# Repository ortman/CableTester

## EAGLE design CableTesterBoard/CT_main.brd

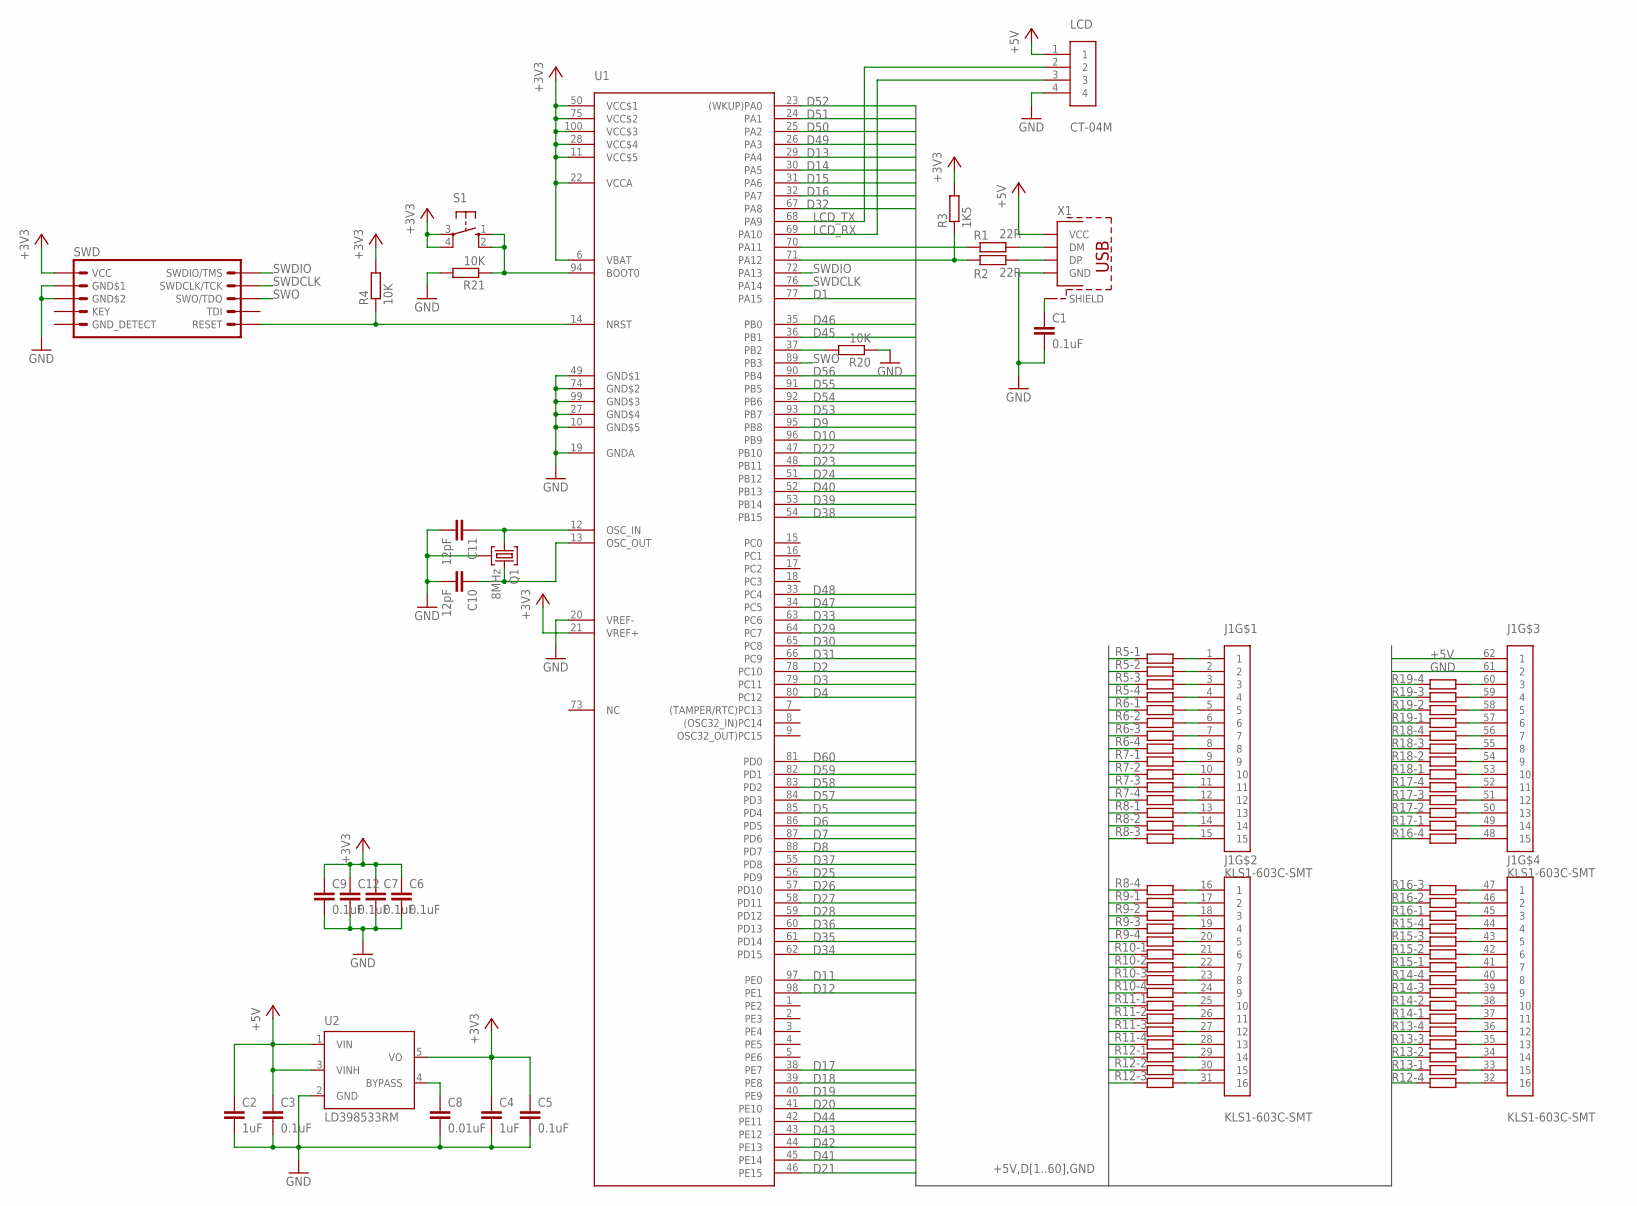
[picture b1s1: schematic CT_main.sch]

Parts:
C1, C3, C5, C6, C7, C9, C12: 0.1uF; C0603
C2, C4: 1uF; C0603
C8: 0.01uF; C0603
C10, C11: 12pF; C0603
J1: KLS1-603C-SMT
LCD: CT-04M
Q1: 8MHz; KX-7_12.XXXXX
R1, R2: 22R; R0603
R3: 1K5; R0603
R4, R20, R21: 10K; R0603
R5, R6, R7, R8, R9, R10, R11, R12, R13, R14, R15, R16, R17, R18, R19: R_EU_4_R1206; R1206_4
S1: 10-XXDTSM-20; DTSM20
SWD: JTAG/SWD_10PIN; ML10
U1: STM32F1xx; LQFP100
U2: LD398533RM; SOT23-5L
X1: USBMICRO-B; MOLEX-47364-0001

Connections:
+3V3: C4.1, C5.1, C6.1, C7.1, C9.1, C12.1, R3.2, R4.2, S1.3, S1.4 (P1), SWD.1 (VCC), U1.6 (VBAT), U1.11 (VCC$5), U1.21 (VREF+), U1.22 (VCCA), U1.28 (VCC$4), U1.50 (VCC$1), U1.75 (VCC$2), U1.100 (VCC$3), U2.5 (VO)
+5V: C2.1, C3.1, J1.62 (1), LCD.1, U2.1 (VIN), U2.3 (VINH), X1.1 (VCC)
D1: R5.8 (2), U1.77 (PA15)
D2: R5.7 (2), U1.78 (PC10)
D3: R5.6 (2), U1.79 (PC11)
D4: R5.5 (2), U1.80 (PC12)
D5: R6.8 (2), U1.85 (PD4)
D6: R6.7 (2), U1.86 (PD5)
D7: R6.6 (2), U1.87 (PD6)
D8: R6.5 (2), U1.88 (PD7)
D9: R7.8 (2), U1.95 (PB8)
D10: R7.7 (2), U1.96 (PB9)
D11: R7.6 (2), U1.97 (PE0)
D12: R7.5 (2), U1.98 (PE1)
D13: R8.8 (2), U1.29 (PA4)
D14: R8.7 (2), U1.30 (PA5)
D15: R8.6 (2), U1.31 (PA6)
D16: R8.5 (2), U1.32 (PA7)
D17: R9.8 (2), U1.38 (PE7)
D18: R9.7 (2), U1.39 (PE8)
D19: R9.6 (2), U1.40 (PE9)
D20: R9.5 (2), U1.41 (PE10)
D21: R10.8 (2), U1.46 (PE15)
D22: R10.7 (2), U1.47 (PB10)
D23: R10.6 (2), U1.48 (PB11)
D24: R10.5 (2), U1.51 (PB12)
D25: R11.8 (2), U1.56 (PD9)
D26: R11.7 (2), U1.57 (PD10)
D27: R11.6 (2), U1.58 (PD11)
D28: R11.5 (2), U1.59 (PD12)
D29: R12.8 (2), U1.64 (PC7)
D30: R12.7 (2), U1.65 (PC8)
D31: R12.6 (2), U1.66 (PC9)
D32: R12.5 (2), U1.67 (PA8)
D33: R13.1, U1.63 (PC6)
D34: R13.2 (1), U1.62 (PD15)
D35: R13.3 (1), U1.61 (PD14)
D36: R13.4 (1), U1.60 (PD13)
D37: R14.1, U1.55 (PD8)
D38: R14.2 (1), U1.54 (PB15)
D39: R14.3 (1), U1.53 (PB14)
D40: R14.4 (1), U1.52 (PB13)
D41: R15.1, U1.45 (PE14)
D42: R15.2 (1), U1.44 (PE13)
D43: R15.3 (1), U1.43 (PE12)
D44: R15.4 (1), U1.42 (PE11)
D45: R16.1, U1.36 (PB1)
D46: R16.2 (1), U1.35 (PB0)
D47: R16.3 (1), U1.34 (PC5)
D48: R16.4 (1), U1.33 (PC4)
D49: R17.1, U1.26 (PA3)
D50: R17.2 (1), U1.25 (PA2)
D51: R17.3 (1), U1.24 (PA1)
D52: R17.4 (1), U1.23 ((WKUP)PA0)
D53: R18.1, U1.93 (PB7)
D54: R18.2 (1), U1.92 (PB6)
D55: R18.3 (1), U1.91 (PB5)
D56: R18.4 (1), U1.90 (PB4)
D57: R19.1, U1.84 (PD3)
D58: R19.2 (1), U1.83 (PD2)
D59: R19.3 (1), U1.82 (PD1)
D60: R19.4 (1), U1.81 (PD0)
GND: C1.2, C2.2, C3.2, C4.2, C5.2, C6.2, C7.2, C8.2, C9.2, C10.2, C11.2, C12.2, J1.61 (2), LCD.4, Q1.2, Q1.4 (2), R20.1, R21.2, SWD.3 (GND$1), SWD.5 (GND$2), U1.10 (GND$5), U1.19 (GNDA), U1.20 (VREF-), U1.27 (GND$4), U1.49 (GND$1), U1.74 (GND$2), U1.99 (GND$3), U2.2 (GND), X1.5 (GND)
GND_DETECT: SWD.9 (GND_DETECT)
LCD_RX: LCD.3, U1.69 (PA10)
LCD_TX: LCD.2, U1.68 (PA9)
unnamed: R1.2, X1.2 (DM)
unnamed: R2.2, X1.3 (DP)
unnamed: C8.1, U2.4 (BYPASS)
unnamed: J1.1, R5.1
unnamed: R1.1, U1.70 (PA11)
unnamed: R2.1, R3.1, U1.71 (PA12)
unnamed: R4.1, SWD.10 (RESET), U1.14 (NRST)
unnamed: C10.1, Q1.3, U1.13 (OSC_OUT)
unnamed: C11.1, Q1.1, U1.12 (OSC_IN)
unnamed: J1.2, R5.2 (1)
unnamed: J1.3, R5.3 (1)
unnamed: J1.4, R5.4 (1)
unnamed: J1.8, R6.4 (1)
unnamed: J1.7, R6.3 (1)
unnamed: J1.6, R6.2 (1)
unnamed: J1.5, R6.1
unnamed: J1.9, R7.1
unnamed: J1.10, R7.2 (1)
unnamed: J1.11, R7.3 (1)
unnamed: J1.12, R7.4 (1)
unnamed: J1.13, R8.1
unnamed: J1.17 (2), R9.1
unnamed: J1.18 (3), R9.2 (1)
unnamed: J1.19 (4), R9.3 (1)
unnamed: J1.20 (5), R9.4 (1)
unnamed: J1.21 (6), R10.1
unnamed: J1.22 (7), R10.2 (1)
unnamed: J1.23 (8), R10.3 (1)
unnamed: J1.27 (12), R11.3 (1)
unnamed: J1.28 (13), R11.4 (1)
unnamed: J1.29 (14), R12.1
unnamed: J1.30 (15), R12.2 (1)
unnamed: J1.31 (16), R12.3 (1)
unnamed: J1.26 (11), R11.2 (1)
unnamed: J1.25 (10), R11.1
unnamed: J1.24 (9), R10.4 (1)
unnamed: J1.14, R8.2 (1)
unnamed: J1.15, R8.3 (1)
unnamed: J1.16 (1), R8.4 (1)
unnamed: J1.32 (16), R12.4 (1)
unnamed: J1.33 (15), R13.8 (2)
unnamed: J1.34 (14), R13.7 (2)
unnamed: J1.35 (13), R13.6 (2)
unnamed: J1.36 (12), R13.5 (2)
unnamed: J1.37 (11), R14.8 (2)
unnamed: J1.38 (10), R14.7 (2)
unnamed: J1.39 (9), R14.6 (2)
unnamed: J1.40 (8), R14.5 (2)
unnamed: J1.41 (7), R15.8 (2)
unnamed: J1.42 (6), R15.7 (2)
unnamed: J1.43 (5), R15.6 (2)
unnamed: J1.44 (4), R15.5 (2)
unnamed: J1.45 (3), R16.8 (2)
unnamed: J1.46 (2), R16.7 (2)
unnamed: J1.47 (1), R16.6 (2)
unnamed: J1.60 (3), R19.5 (2)
unnamed: J1.59 (4), R19.6 (2)
unnamed: J1.58 (5), R19.7 (2)
unnamed: J1.57 (6), R19.8 (2)
unnamed: J1.56 (7), R18.5 (2)
unnamed: J1.55 (8), R18.6 (2)
unnamed: J1.54 (9), R18.7 (2)
unnamed: J1.53 (10), R18.8 (2)
unnamed: J1.52 (11), R17.5 (2)
unnamed: J1.51 (12), R17.6 (2)
unnamed: J1.50 (13), R17.7 (2)
unnamed: J1.49 (14), R17.8 (2)
unnamed: J1.48 (15), R16.5 (2)
unnamed: R20.2, U1.37 (PB2)
unnamed: R21.1, S1.1 (S), S1.2 (S1), U1.94 (BOOT0)
SHIELD: C1.1, X1.GND1 (SHIELD), X1.GND2 (SHIELD), X1.GND3 (SHIELD), X1.GND4 (SHIELD)
SWDCLK: SWD.4 (SWDCLK/TCK), U1.76 (PA14)
SWDIO: SWD.2 (SWDIO/TMS), U1.72 (PA13)
SWO: SWD.6 (SWO/TDO), U1.89 (PB3)

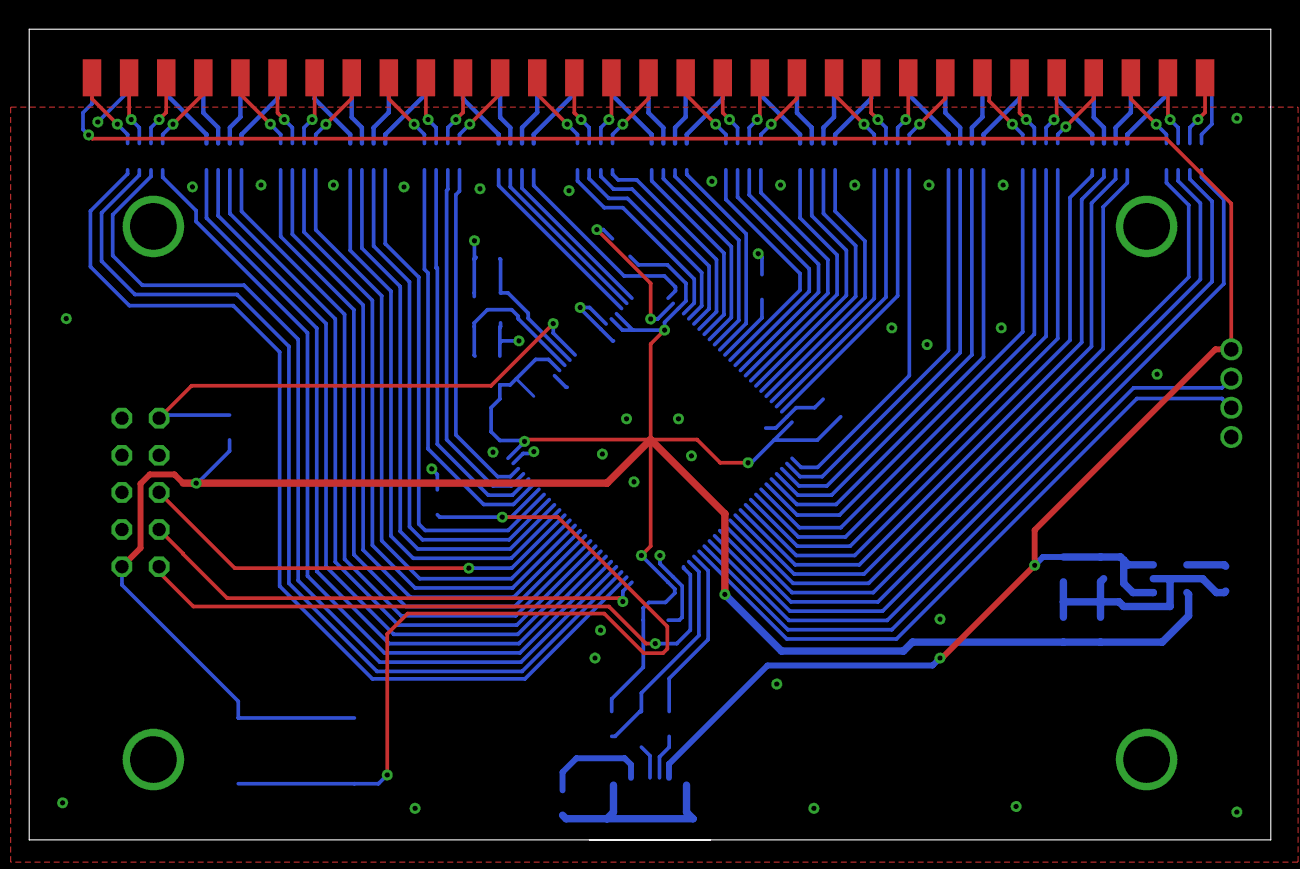
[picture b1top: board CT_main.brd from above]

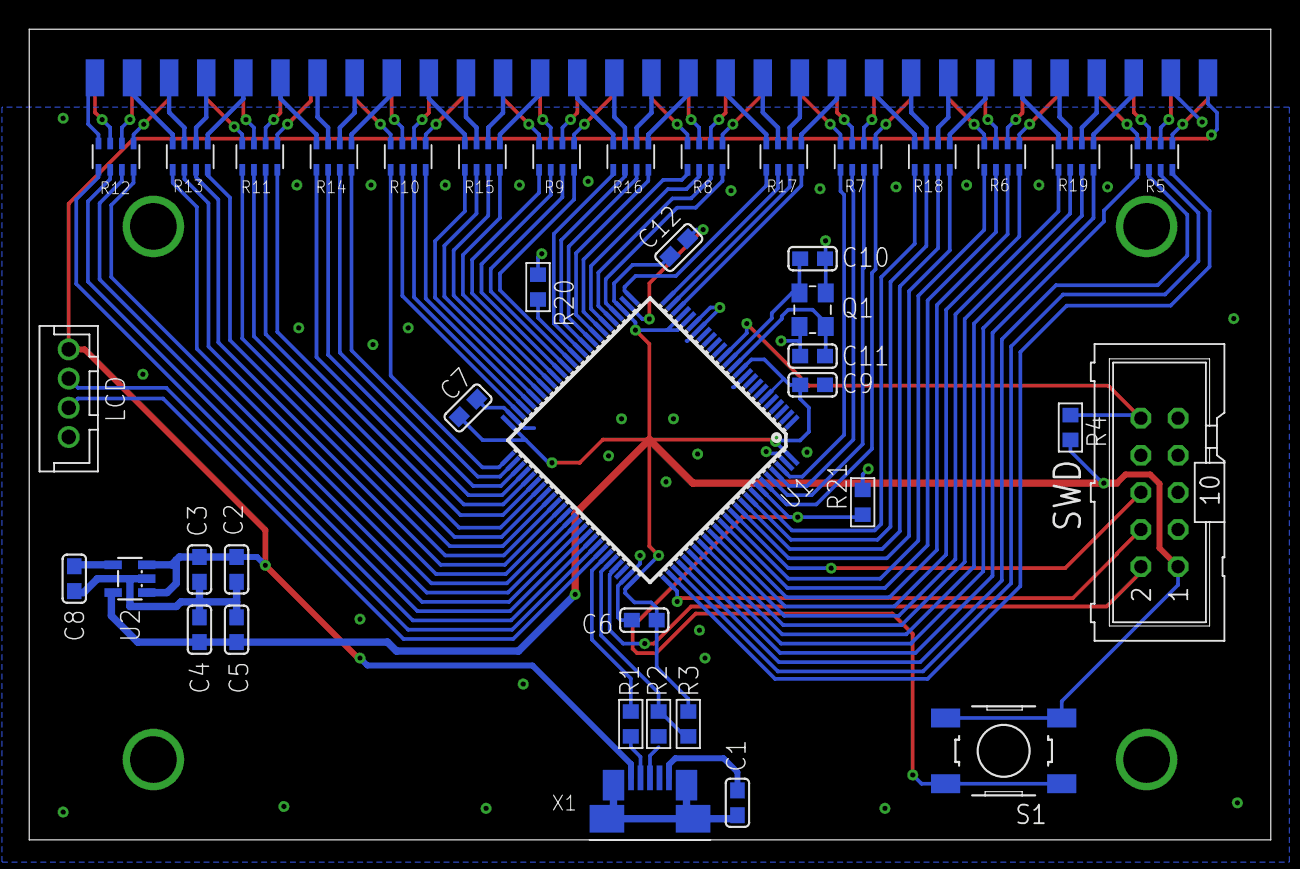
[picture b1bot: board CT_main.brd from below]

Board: 2 copper layers, 85.0 x 55.5 mm, 41 parts (40 on the bottom side), 139 nets.

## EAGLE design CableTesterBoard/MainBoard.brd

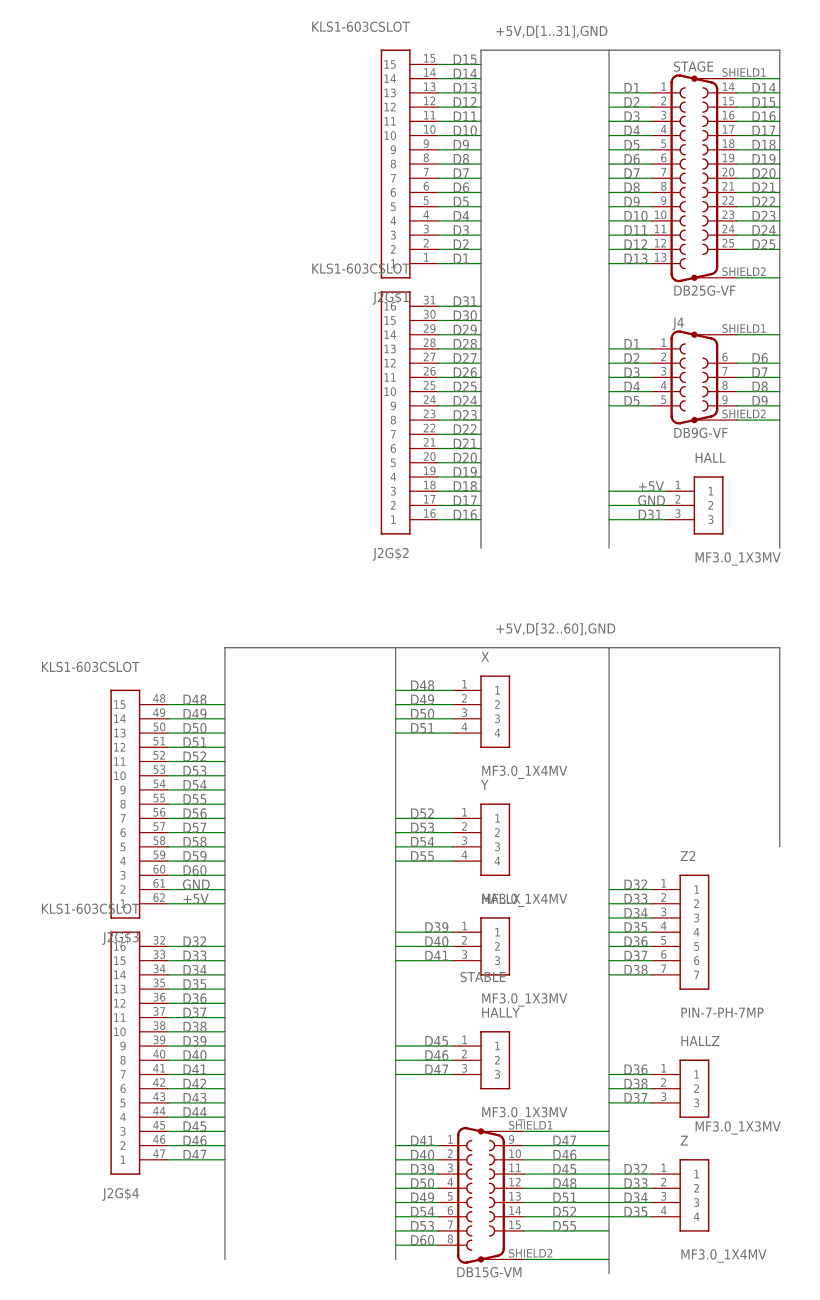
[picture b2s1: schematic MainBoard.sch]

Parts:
HALL: MF3.0_1X3MV
HALLX: MF3.0_1X3MV
HALLY: MF3.0_1X3MV
HALLZ: MF3.0_1X3MV
J2: KLS1-603CSLOT; KLS1-603C-SLOT
J4: DB9G-VF; DB9G-F
STABLE: DB15G-VM; DS1034-15
STAGE: DB25G-VF; DB25G-F
X: MF3.0_1X4MV
Y: MF3.0_1X4MV
Z: MF3.0_1X4MV
Z2: PIN-7-PH-7MP; PH-7MP

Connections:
+5V: HALL.1, J2.62 (1)
D1: J2.1, J4.1, STAGE.1
D2: J2.2, J4.2, STAGE.2
D3: J2.3, J4.3, STAGE.3
D4: J2.4, J4.4, STAGE.4
D5: J2.5, J4.5, STAGE.5
D6: J2.6, J4.6, STAGE.6
D7: J2.7, J4.7, STAGE.7
D8: J2.8, J4.8, STAGE.8
D9: J2.9, J4.9, STAGE.9
D10: J2.10, STAGE.10
D11: J2.11, STAGE.11
D12: J2.12, STAGE.12
D13: J2.13, STAGE.13
D14: J2.14, STAGE.14
D15: J2.15, STAGE.15
D16: J2.16 (1), STAGE.16
D17: J2.17 (2), STAGE.17
D18: J2.18 (3), STAGE.18
D19: J2.19 (4), STAGE.19
D20: J2.20 (5), STAGE.20
D21: J2.21 (6), STAGE.21
D22: J2.22 (7), STAGE.22
D23: J2.23 (8), STAGE.23
D24: J2.24 (9), STAGE.24
D25: J2.25 (10), STAGE.25
D26: J2.26 (11)
D27: J2.27 (12)
D28: J2.28 (13)
D29: J2.29 (14)
D30: J2.30 (15)
D31: HALL.3, J2.31 (16)
D32: J2.32 (16), Z.1, Z2.1
D33: J2.33 (15), Z.2, Z2.2
D34: J2.34 (14), Z.3, Z2.3
D35: J2.35 (13), Z.4, Z2.4
D36: HALLZ.1, J2.36 (12), Z2.5
D37: HALLZ.3, J2.37 (11), Z2.6
D38: HALLZ.2, J2.38 (10), Z2.7
D39: HALLX.1, J2.39 (9), STABLE.3
D40: HALLX.2, J2.40 (8), STABLE.2
D41: HALLX.3, J2.41 (7), STABLE.1
D42: J2.42 (6)
D43: J2.43 (5)
D44: J2.44 (4)
D45: HALLY.1, J2.45 (3), STABLE.11
D46: HALLY.2, J2.46 (2), STABLE.10
D47: HALLY.3, J2.47 (1), STABLE.9
D48: J2.48 (15), STABLE.12, X.1
D49: J2.49 (14), STABLE.5, X.2
D50: J2.50 (13), STABLE.4, X.3
D51: J2.51 (12), STABLE.13, X.4
D52: J2.52 (11), STABLE.14, Y.1
D53: J2.53 (10), STABLE.7, Y.2
D54: J2.54 (9), STABLE.6, Y.3
D55: J2.55 (8), STABLE.15, Y.4
D56: J2.56 (7)
D57: J2.57 (6)
D58: J2.58 (5)
D59: J2.59 (4)
D60: J2.60 (3), STABLE.8
GND: HALL.2, J2.61 (2), J4.SHIELD1 (G1), J4.SHIELD2 (G2), STABLE.SHIELD1 (G1), STABLE.SHIELD2 (G2), STAGE.SHIELD1 (G1), STAGE.SHIELD2 (G2)

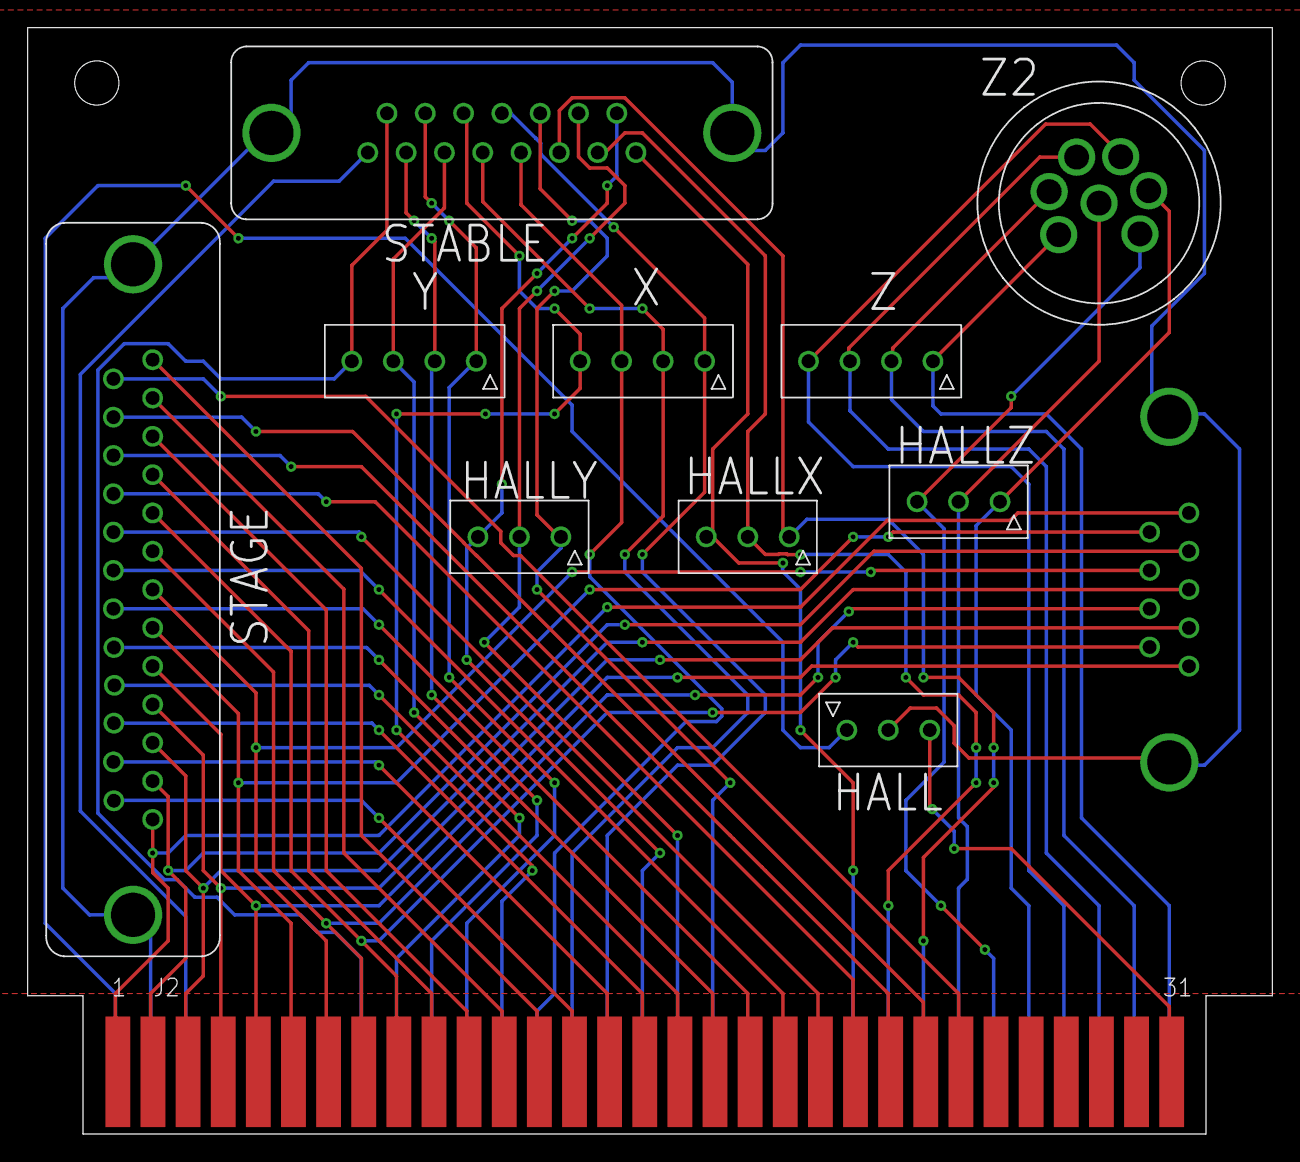
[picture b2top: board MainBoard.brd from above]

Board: 2 copper layers, 90.0 x 80.0 mm, 12 parts (1 on the bottom side), 50 nets.

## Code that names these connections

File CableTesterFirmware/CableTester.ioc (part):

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Mcu.Name=STM32F103V(8-B)Tx
Mcu.Package=LQFP100
Mcu.UserName=STM32F103V8Tx
PA0-WKUP.GPIOParameters=GPIO_PuPd,GPIO_Label
PA0-WKUP.GPIO_Label=D52
PA0-WKUP.GPIO_PuPd=GPIO_PULLDOWN
PA0-WKUP.Signal=GPIO_Input
PA1.GPIOParameters=GPIO_PuPd,GPIO_Label
PA1.GPIO_Label=D51
PA1.GPIO_PuPd=GPIO_PULLDOWN
PA1.Signal=GPIO_Input
PA10.Mode=Asynchronous
PA10.Signal=USART1_RX
PA11.Mode=Device
PA11.Signal=USB_DM
PA12.Mode=Device
PA12.Signal=USB_DP
PA13.Mode=Trace_Asynchronous_SW
PA13.Signal=SYS_JTMS-SWDIO
PA14.Mode=Trace_Asynchronous_SW
PA14.Signal=SYS_JTCK-SWCLK
PA15.GPIOParameters=GPIO_PuPd,GPIO_Label
PA15.GPIO_Label=D1
PA15.GPIO_PuPd=GPIO_PULLDOWN
PA15.Signal=GPIO_Input
PA2.GPIOParameters=GPIO_PuPd,GPIO_Label
PA2.GPIO_Label=D50
PA2.GPIO_PuPd=GPIO_PULLDOWN
PA2.Signal=GPIO_Input
PA3.GPIOParameters=GPIO_PuPd,GPIO_Label
PA3.GPIO_Label=D49
PA3.GPIO_PuPd=GPIO_PULLDOWN
PA3.Signal=GPIO_Input
PA4.GPIOParameters=GPIO_PuPd,GPIO_Label
PA4.GPIO_Label=D13
PA4.GPIO_PuPd=GPIO_PULLDOWN
PA4.Signal=GPIO_Input
PA5.GPIOParameters=GPIO_PuPd,GPIO_Label
PA5.GPIO_Label=D14
PA5.GPIO_PuPd=GPIO_PULLDOWN
PA5.Signal=GPIO_Input
PA6.GPIOParameters=GPIO_PuPd,GPIO_Label
PA6.GPIO_Label=D15
PA6.GPIO_PuPd=GPIO_PULLDOWN
PA6.Signal=GPIO_Input
PA7.GPIOParameters=GPIO_PuPd,GPIO_Label
PA7.GPIO_Label=D16
PA7.GPIO_PuPd=GPIO_PULLDOWN
PA7.Signal=GPIO_Input
PA8.GPIOParameters=GPIO_PuPd,GPIO_Label
PA8.GPIO_Label=D32
PA8.GPIO_PuPd=GPIO_PULLDOWN
PA8.Signal=GPIO_Input
PA9.Mode=Asynchronous
PA9.Signal=USART1_TX
PB0.GPIOParameters=GPIO_PuPd,GPIO_Label
PB0.GPIO_Label=D46
PB0.GPIO_PuPd=GPIO_PULLDOWN
PB0.Signal=GPIO_Input
PB1.GPIOParameters=GPIO_PuPd,GPIO_Label
PB1.GPIO_Label=D45
PB1.GPIO_PuPd=GPIO_PULLDOWN
PB1.Signal=GPIO_Input
PB10.GPIOParameters=GPIO_PuPd,GPIO_Label
PB10.GPIO_Label=D22
PB10.GPIO_PuPd=GPIO_PULLDOWN
PB10.Signal=GPIO_Input
PB11.GPIOParameters=GPIO_PuPd,GPIO_Label
PB11.GPIO_Label=D23
PB11.GPIO_PuPd=GPIO_PULLDOWN
PB11.Signal=GPIO_Input
PB12.GPIOParameters=GPIO_PuPd,GPIO_Label
PB12.GPIO_Label=D24
PB12.GPIO_PuPd=GPIO_PULLDOWN
PB12.Signal=GPIO_Input
PB13.GPIOParameters=GPIO_PuPd,GPIO_Label
PB13.GPIO_Label=D40
PB13.GPIO_PuPd=GPIO_PULLDOWN
PB13.Signal=GPIO_Input
PB14.GPIOParameters=GPIO_PuPd,GPIO_Label
PB14.GPIO_Label=D39
PB14.GPIO_PuPd=GPIO_PULLDOWN
PB14.Signal=GPIO_Input
PB15.GPIOParameters=GPIO_PuPd,GPIO_Label
PB15.GPIO_Label=D38
PB15.GPIO_PuPd=GPIO_PULLDOWN
PB15.Signal=GPIO_Input
PB3.Mode=Trace_Asynchronous_SW
PB3.Signal=SYS_JTDO-TRACESWO
PB4.GPIOParameters=GPIO_PuPd,GPIO_Label
PB4.GPIO_Label=D56
PB4.GPIO_PuPd=GPIO_PULLDOWN
PB4.Signal=GPIO_Input
PB5.GPIOParameters=GPIO_PuPd,GPIO_Label
PB5.GPIO_Label=D55
PB5.GPIO_PuPd=GPIO_PULLDOWN
PB5.Signal=GPIO_Input
PB6.GPIOParameters=GPIO_PuPd,GPIO_Label
PB6.GPIO_Label=D54
PB6.GPIO_PuPd=GPIO_PULLDOWN
PB6.Signal=GPIO_Input
PB7.GPIOParameters=GPIO_PuPd,GPIO_Label
PB7.GPIO_Label=D53
PB7.GPIO_PuPd=GPIO_PULLDOWN
PB7.Signal=GPIO_Input
PB8.GPIOParameters=GPIO_PuPd,GPIO_Label
PB8.GPIO_Label=D9
PB8.GPIO_PuPd=GPIO_PULLDOWN
PB8.Signal=GPIO_Input
PB9.GPIOParameters=GPIO_PuPd,GPIO_Label
PB9.GPIO_Label=D10
PB9.GPIO_PuPd=GPIO_PULLDOWN
PB9.Signal=GPIO_Input
PC10.GPIOParameters=GPIO_PuPd,GPIO_Label
PC10.GPIO_Label=D2
PC10.GPIO_PuPd=GPIO_PULLDOWN
PC10.Signal=GPIO_Input
PC11.GPIOParameters=GPIO_PuPd,GPIO_Label
PC11.GPIO_Label=D3
PC11.GPIO_PuPd=GPIO_PULLDOWN
PC11.Signal=GPIO_Input
PC12.GPIOParameters=GPIO_PuPd,GPIO_Label
PC12.GPIO_Label=D4
PC12.GPIO_PuPd=GPIO_PULLDOWN
PC12.Signal=GPIO_Input
PC4.GPIOParameters=GPIO_PuPd,GPIO_Label
PC4.GPIO_Label=D48
PC4.GPIO_PuPd=GPIO_PULLDOWN
PC4.Signal=GPIO_Input
PC5.GPIOParameters=GPIO_PuPd,GPIO_Label
PC5.GPIO_Label=D47
PC5.GPIO_PuPd=GPIO_PULLDOWN
PC5.Signal=GPIO_Input
PC6.GPIOParameters=GPIO_PuPd,GPIO_Label
PC6.GPIO_Label=D33
PC6.GPIO_PuPd=GPIO_PULLDOWN
PC6.Signal=GPIO_Input
PC7.GPIOParameters=GPIO_PuPd,GPIO_Label
PC7.GPIO_Label=D29
PC7.GPIO_PuPd=GPIO_PULLDOWN
PC7.Signal=GPIO_Input
PC8.GPIOParameters=GPIO_PuPd,GPIO_Label
PC8.GPIO_Label=D30
PC8.GPIO_PuPd=GPIO_PULLDOWN
PC8.Signal=GPIO_Input
PC9.GPIOParameters=GPIO_Label
PC9.GPIO_Label=D31
PC9.Signal=GPIO_Output
PD0.GPIOParameters=GPIO_PuPd,GPIO_Label
PD0.GPIO_Label=D60
PD0.GPIO_PuPd=GPIO_PULLDOWN
PD0.Signal=GPIO_Input
PD1.GPIOParameters=GPIO_PuPd,GPIO_Label
PD1.GPIO_Label=D59
PD1.GPIO_PuPd=GPIO_PULLDOWN
PD1.Signal=GPIO_Input
PD10.GPIOParameters=GPIO_PuPd,GPIO_Label
PD10.GPIO_Label=D26
PD10.GPIO_PuPd=GPIO_PULLDOWN
PD10.Signal=GPIO_Input
PD11.GPIOParameters=GPIO_PuPd,GPIO_Label
PD11.GPIO_Label=D27
PD11.GPIO_PuPd=GPIO_PULLDOWN
PD11.Signal=GPIO_Input
PD12.GPIOParameters=GPIO_PuPd,GPIO_Label
PD12.GPIO_Label=D28
PD12.GPIO_PuPd=GPIO_PULLDOWN
PD12.Signal=GPIO_Input
PD13.GPIOParameters=GPIO_PuPd,GPIO_Label
PD13.GPIO_Label=D36
PD13.GPIO_PuPd=GPIO_PULLDOWN
PD13.Signal=GPIO_Input
PD14.GPIOParameters=GPIO_PuPd,GPIO_Label
PD14.GPIO_Label=D35
PD14.GPIO_PuPd=GPIO_PULLDOWN
PD14.Signal=GPIO_Input
PD15.GPIOParameters=GPIO_PuPd,GPIO_Label
PD15.GPIO_Label=D34
PD15.GPIO_PuPd=GPIO_PULLDOWN
PD15.Signal=GPIO_Input
PD2.GPIOParameters=GPIO_PuPd,GPIO_Label
PD2.GPIO_Label=D58
PD2.GPIO_PuPd=GPIO_PULLDOWN
PD2.Signal=GPIO_Input
PD3.GPIOParameters=GPIO_PuPd,GPIO_Label
PD3.GPIO_Label=D57
PD3.GPIO_PuPd=GPIO_PULLDOWN
PD3.Signal=GPIO_Input
PD4.GPIOParameters=GPIO_PuPd,GPIO_Label
PD4.GPIO_Label=D5
PD4.GPIO_PuPd=GPIO_PULLDOWN
PD4.Signal=GPIO_Input
PD5.GPIOParameters=GPIO_PuPd,GPIO_Label
PD5.GPIO_Label=D6
PD5.GPIO_PuPd=GPIO_PULLDOWN
PD5.Signal=GPIO_Input
PD6.GPIOParameters=GPIO_PuPd,GPIO_Label
PD6.GPIO_Label=D7
PD6.GPIO_PuPd=GPIO_PULLDOWN
PD6.Signal=GPIO_Input
PD7.GPIOParameters=GPIO_PuPd,GPIO_Label
PD7.GPIO_Label=D8
PD7.GPIO_PuPd=GPIO_PULLDOWN
PD7.Signal=GPIO_Input
PD8.GPIOParameters=GPIO_PuPd,GPIO_Label
PD8.GPIO_Label=D37
PD8.GPIO_PuPd=GPIO_PULLDOWN
PD8.Signal=GPIO_Input
PD9.GPIOParameters=GPIO_PuPd,GPIO_Label
PD9.GPIO_Label=D25
PD9.GPIO_PuPd=GPIO_PULLDOWN
PD9.Signal=GPIO_Input
PE0.GPIOParameters=GPIO_PuPd,GPIO_Label
PE0.GPIO_Label=D11
PE0.GPIO_PuPd=GPIO_PULLDOWN
PE0.Signal=GPIO_Input
PE1.GPIOParameters=GPIO_PuPd,GPIO_Label
PE1.GPIO_Label=D12
PE1.GPIO_PuPd=GPIO_PULLDOWN
PE1.Signal=GPIO_Input
PE10.GPIOParameters=GPIO_PuPd,GPIO_Label
PE10.GPIO_Label=D20
PE10.GPIO_PuPd=GPIO_PULLDOWN
PE10.Signal=GPIO_Input
PE11.GPIOParameters=GPIO_PuPd,GPIO_Label
PE11.GPIO_Label=D44
PE11.GPIO_PuPd=GPIO_PULLDOWN
PE11.Signal=GPIO_Input
PE12.GPIOParameters=GPIO_PuPd,GPIO_Label
PE12.GPIO_Label=D43
PE12.GPIO_PuPd=GPIO_PULLDOWN
PE12.Signal=GPIO_Input
PE13.GPIOParameters=GPIO_PuPd,GPIO_Label
PE13.GPIO_Label=D42
PE13.GPIO_PuPd=GPIO_PULLDOWN
PE13.Signal=GPIO_Input
PE14.GPIOParameters=GPIO_PuPd,GPIO_Label
PE14.GPIO_Label=D41
PE14.GPIO_PuPd=GPIO_PULLDOWN
PE14.Signal=GPIO_Input
PE15.GPIOParameters=GPIO_PuPd,GPIO_Label
PE15.GPIO_Label=D21
PE15.GPIO_PuPd=GPIO_PULLDOWN
PE15.Signal=GPIO_Input
PE7.GPIOParameters=GPIO_PuPd,GPIO_Label
PE7.GPIO_Label=D17
PE7.GPIO_PuPd=GPIO_PULLDOWN
PE7.Signal=GPIO_Input
PE8.GPIOParameters=GPIO_PuPd,GPIO_Label
PE8.GPIO_Label=D18
PE8.GPIO_PuPd=GPIO_PULLDOWN
PE8.Signal=GPIO_Input
PE9.GPIOParameters=GPIO_PuPd,GPIO_Label
PE9.GPIO_Label=D19
PE9.GPIO_PuPd=GPIO_PULLDOWN
PE9.Signal=GPIO_Input
RCC.SYSCLKFreq_VALUE=72000000
RCC.SYSCLKSource=RCC_SYSCLKSOURCE_PLLCLK
board=custom

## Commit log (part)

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2023-09-14 first
2025-01-22 Second commit
2025-01-22 Removed Viewer.lay
2025-01-22 Litle fixes
2025-01-22 Add window snapshot
2025-01-27 Subsampling, object selector on Viewer
2025-01-27 Fixed text position of cable name
2025-01-27 Fixed layout
2025-01-27 Fixed cable names
2025-01-27 Select a wire in Viewer
2025-01-28 Rename to CableTesterDesktop
2025-01-28 Add translation file. Load Cables from application folder
2025-01-29 Creating/removing the Wire
2025-01-29 Add tools to layout
2025-01-29 Create new Nextion interface
2025-01-29 Save PNG image for Nextion display
2025-01-30 Fixed all text size
2025-01-30 Choice of color of creating wire. Fixed draw creating wire on right.
2025-01-30 Drawing wire on selecter layer
2025-01-30 Union WISP and COVER to CABLE
2025-01-30 Fixed parser
2025-01-30 Refactor Wire.Draw()
2025-01-30 Fixed drawing wires
2025-01-30 Added test cables
2025-01-31 Add board and firmware
2025-01-31 Refactoring Wire.Draw()
2025-01-31 Select any objects
2025-01-31 Fixed include translation file
2025-02-01 Removing Wires, Connectors, Cables
2025-02-02 Draw empty cables
2025-02-02 Added destructors on classes. Heap fixes.
2025-02-02 Fixed bug Load project
2025-02-02 Refactor DrawBezier
2025-02-04 Generate Firmware VSCode project from CubeMX
2025-02-04 remove build
2025-02-13 Fixed rendering wires of left-left of right-right connectors
2025-02-13 Refactoring: Remove unused parameters
2025-02-13 Changing color of wires and cables
2025-02-13 Cable name of white text if cable color is dark
2025-02-13 Show parent cable on editor
2025-02-13 Added properties widget
2025-02-14 No special colors
2025-02-14 Property editor
2025-02-14 Add WinUSB device library
2025-02-14 Firmware: WinUSB
2025-02-17 Add new cables. Add new connector. Parameters.
2025-02-17 Added new cables and connectors to ViewerSelector
2025-02-17 Remove parameter fields on create window
2025-02-19 Load and save to binary files
2025-02-19 Fixed trim cable names
2025-02-19 Draw coper wire
2025-02-19 Fixed cancel of removing connector
2025-02-20 Property editor: name
2025-02-20 Drawing not connected wires
2025-02-21 Draw coper line
2025-02-21 Fixed colors on Dark theme. Fixed focus of Viewer control. Add new preview for Readme.
2025-02-21 WinUSB firmware
2025-02-24 firmware USB
2025-02-24 rename firmware tasr
2025-02-25 Debug winUSB device
2025-02-26 RTT debug connected
2025-03-06 FW: WinUSB
2025-05-26 Update HAL libraries
2025-11-01 Added testerPin to Connector. Created "Cable" folder if not exist
2025-11-01 Up/Down moving buttons
2025-11-07 Fixed unicede names. Fixed sorting a wires. Fixed read file errors. Added a Tester pin map.
2025-11-07 Refreshing the viewer after sorting
2025-11-10 Refactor draw of wires
2025-11-10 Fixed export image. Update images in HMI
